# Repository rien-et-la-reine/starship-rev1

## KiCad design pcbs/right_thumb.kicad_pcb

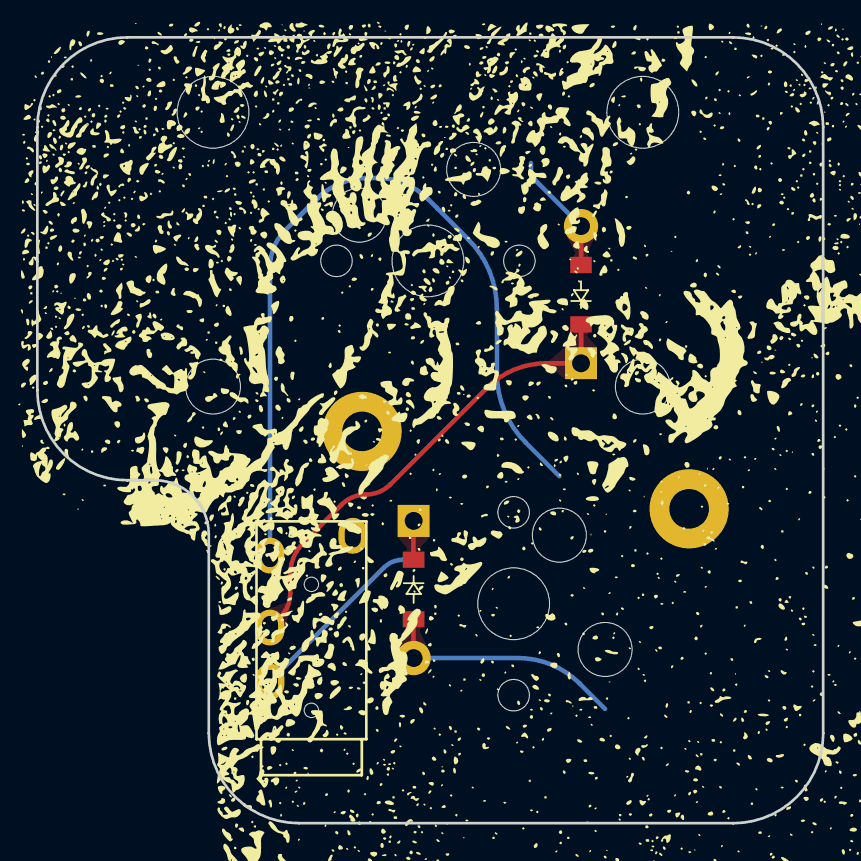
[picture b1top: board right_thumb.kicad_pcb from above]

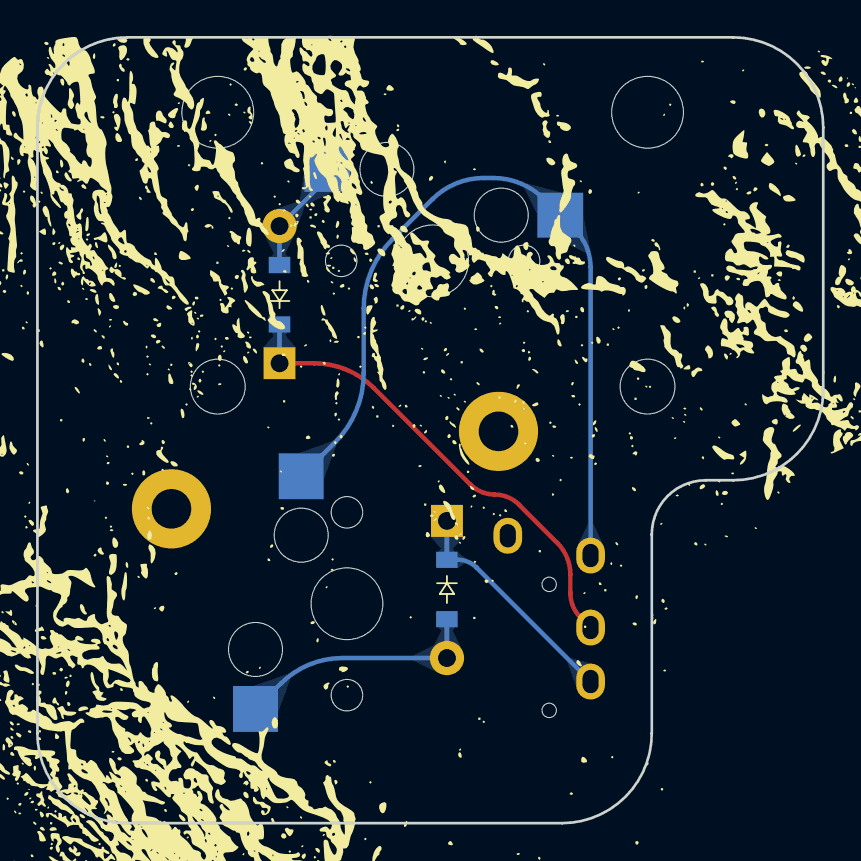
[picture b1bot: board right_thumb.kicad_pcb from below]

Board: 2 copper layers, 43.7 x 43.7 mm, 4 parts (2 on the bottom side), 3 nets.

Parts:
D22, D23: ComboDiode
S22: MXOnly-1.5U-Hotswap
S23: MXOnly-2U-Hotswap

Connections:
T_COL: S22.1, S23.1
reach_boat: D23.2, S23.2
rest_boat: D22.2, S22.2

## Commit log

2024-11-14 create definition and config files
2024-11-15 added thumb clusters back
2024-11-15 remove thumb cluster
2024-11-15 add thumb cluster
2024-11-16 fix key order
2024-11-16 upload kicad pcb and base stl files
2024-11-17 updated firmware
    updated metadata to indicate zmk studio support and added settings reset file, just in case it's ever needed
2024-11-17 Update right_thumb.kicad_pcb
    rotated stabilizer footprint on left thumb to avoid stablilizer wire interfering with mounting hole
2024-11-17 Flipped Battery Connector
    rotated battery connector on right side around
2026-03-13 36 key default
    plus extra blank layers potentially to be set up in zmk studio later
2026-03-13 Update build.yaml
    apparently it's just nice_nano now
2026-03-14 Update starship.keymap
    idk if all this is necessary maybe just a single whitespace or a single key would do but better safe than sorry
2026-03-14 Update starship.keymap
    shh you didn't see that...i should stop making edits from my phone where going back to reference the actual documentation is mildly more inconvenient to me
2026-03-14 Update starship.keymap
    fixed homerow mod placement
2026-03-14 upload 36 key firmware
2026-03-14 Create starship.keymap
    for nickcoutsos' keymap editor
2026-03-14 Updated starship.keymap
2026-03-14 messing with modmorph for easier access to common symbols
2026-03-15 unreserving reserved layers
